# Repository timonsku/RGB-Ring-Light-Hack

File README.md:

# RGB-Ring-Light-Hack
Info and material to hack common RGB(W) ring lights with your own controller

The hack adds a Raspberry Pi Pico into the original case of the controller with some side cutter modifications and a backpack PCB that adds buttons and mosfets to control the cold and warm white LEDs.

This is based on a RGB ring light that you can buy from AliExpress, Ebay, Amazon etc.
The generic term is "10 Inch RGB Ring Light" or "10 Inch RGB Beauty Light"
The case hack that you can find in this repo is based on the model found from this vendor (affiliate link): https://s.click.aliexpress.com/e/_99rVuu

This is a high quality model of this ring light and I recommend getting that version. You might find cheaper models but they often use a different controller with a smaller case and generally a bit worse built quality, the PCB for the light seems to be generally the same though.

For reproducing you will need a Raspberry Pi Pico, order the PCB in `Case-Hack-PCB` and modify the case with a pair of flat side cutters according to the reference photos in `Case-Modification-Reference`. Beware of the cutouts for the buttons, you need to make them large enough so that the new buttons can fit, otherwise the case will not close well.

To open the case the first time, insert something flat/sharp between the edges of the two halfs and lever them apart, you may need to do that in multiple points before it comes apart. There is no snap fits, its just a pressure fit.

When soldering the PCB, take a look at `Case-Hack-PCB/solder-reference-headers.jpg` you need to trim the headers after soldering and add a header pointing in the opposite direction to the SWD pins for stabilization, those should be soldered first, otherwise its going to be difficult with the button pcb already in place.

I don't have the time to document this in a step by step manner. If anyone reproduces this and would like to do that, PR's are more than welcome.

Original Twitter thread with possibly some more details: https://twitter.com/timonsku/status/1357681117395103746

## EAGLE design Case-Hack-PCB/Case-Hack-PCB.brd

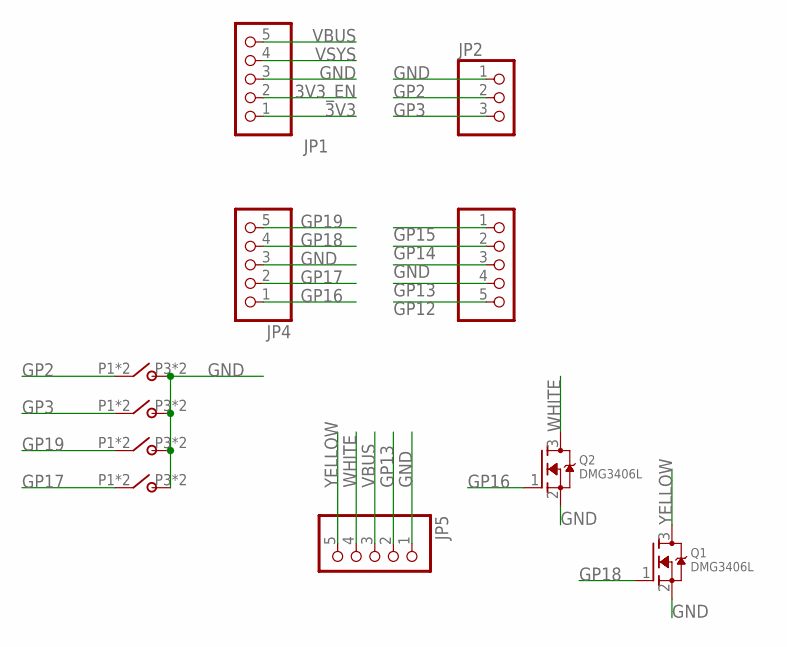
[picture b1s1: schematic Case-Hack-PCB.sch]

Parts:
JP1, JP3, JP4, JP5: HEADER-1X5ROUND; 1X05_ROUND
JP2: HEADER-1X3ROUND; 1X03_ROUND
Q1, Q2: DMG3406L; SOT23-WIDE
U$1, U$2, U$3, U$4: K2-1109SP-B4SA-01

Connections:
3V3: JP1.1
3V3_EN: JP1.2
GND: JP1.3, JP2.1, JP3.3, JP4.3, JP5.1, Q1.2 (S), Q2.2 (S), U$1.P3, U$1.P4, U$2.P3, U$2.P4, U$3.P3, U$3.P4, U$4.P3, U$4.P4
GP2: JP2.2, U$1.P1, U$1.P2
GP3: JP2.3, U$2.P1, U$2.P2
GP12: JP3.5
GP13: JP3.4, JP5.2
GP14: JP3.2
GP15: JP3.1
GP16: JP4.1, Q2.1 (G)
GP17: JP4.2, U$4.P1, U$4.P2
GP18: JP4.4, Q1.1 (G)
GP19: JP4.5, U$3.P1, U$3.P2
VBUS: JP1.5, JP5.3
VSYS: JP1.4
WHITE: JP5.4, Q2.3 (D)
YELLOW: JP5.5, Q1.3 (D)

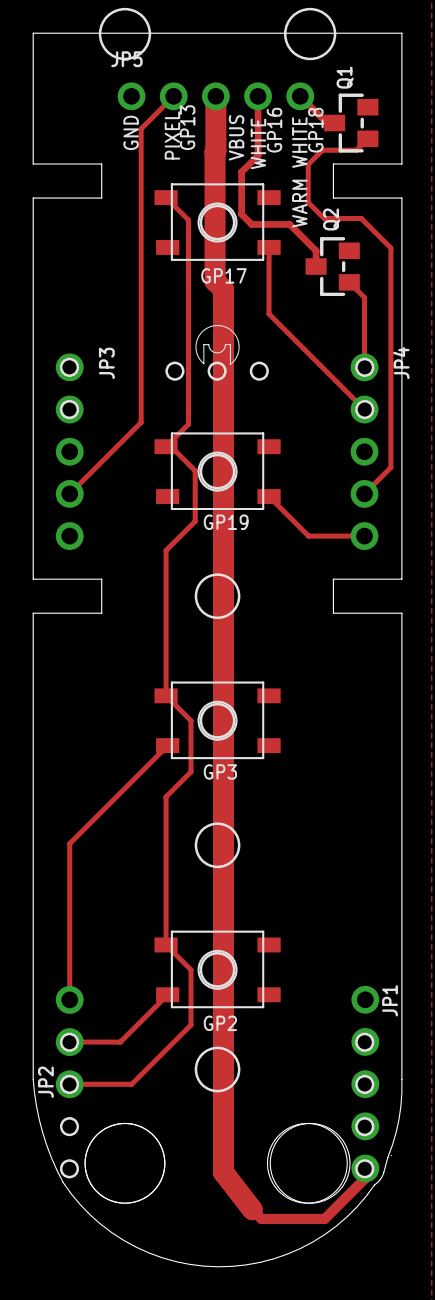
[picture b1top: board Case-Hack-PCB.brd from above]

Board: 2 copper layers, 22.2 x 74.3 mm, 11 parts (0 on the bottom side), 11 nets.

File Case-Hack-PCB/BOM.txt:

Buttons: K2-1109SP-B4SA-01 https://lcsc.com/product-detail/Tactile-Switches_Korean-Hrop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

Mosfet: DMG3406L https://lcsc.com/product-detail/MOSFET_Diodes-Incorporated-D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

Generic 2.54mm Pin headers

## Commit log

2021-03-09 more photos, link to thread
2021-03-09 More details

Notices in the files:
parts and their libraries:
microbuilder: This work is placed in the public domain, and may be freely used for commercial and non-commercial work with the following conditions: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
